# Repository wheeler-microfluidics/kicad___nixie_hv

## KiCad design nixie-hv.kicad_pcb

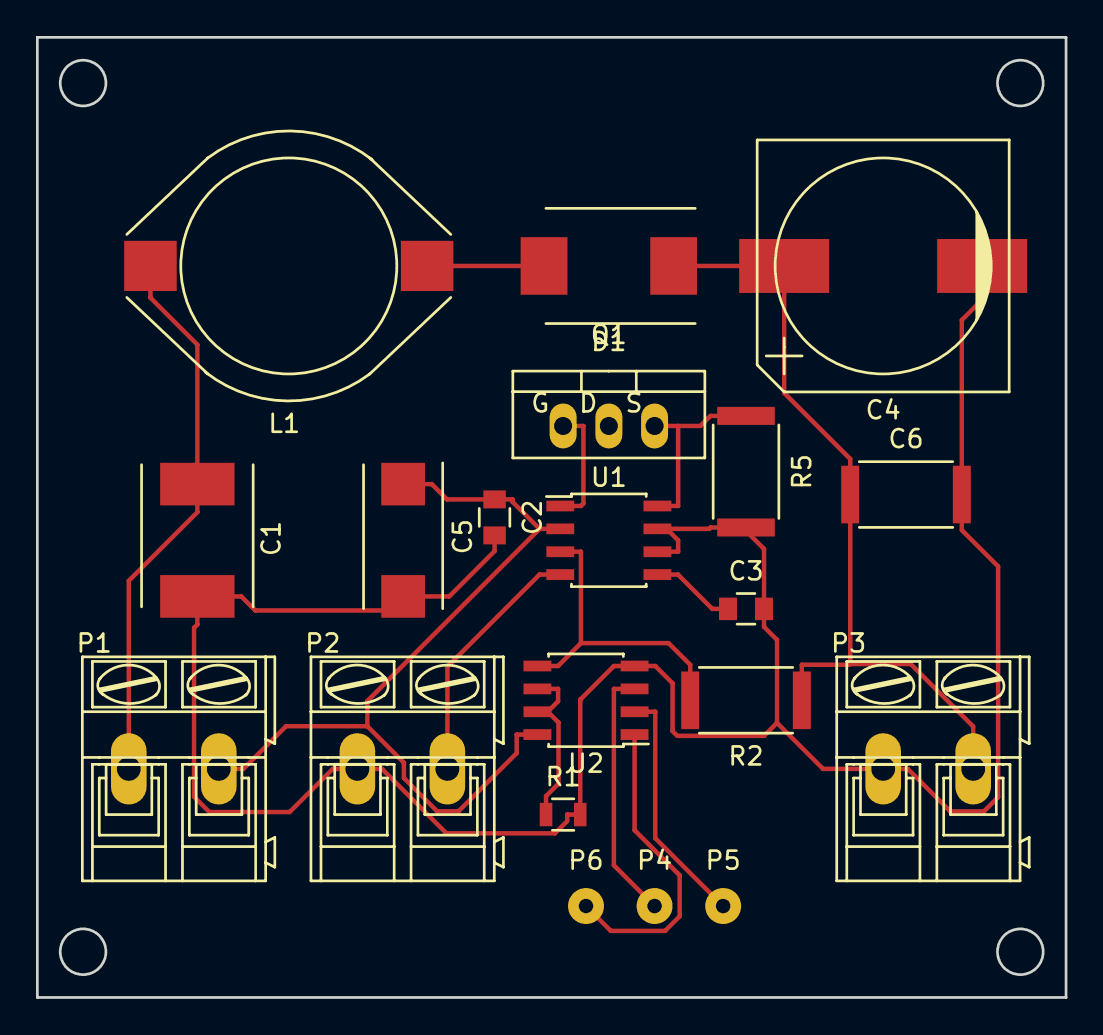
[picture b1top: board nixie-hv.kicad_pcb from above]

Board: 2 copper layers, 57.1 x 53.3 mm, 20 parts (0 on the bottom side), 14 nets.

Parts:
C1: 100uF, 35V; TantalC_SizeE_EIA-7360_Reflow
C2, C3: 100nF; C_0805
C4: 4u7,250V; C_SMD_12mm
C5: 10uF; TantalC_SizeD_EIA-7343_Reflow
C6: 100nF,250V; R_2512
D1: ES2F; DO-214AB
L1: 100uH; Inductor_18.54x15.24
P1: J1; AK300-2
P2: J2; AK300-2
P3: J3; AK300-2
P4, P5, P6: CONN_01X01; SolderWirePad_single_0-8mmDrill
Q1: IRF644PBF; TO-220_FET-GDS_Vertical
R1: 10k; R_0805
R2: 1M5; R_2512
R5: RSENSE; R_2512
U1: MAX1771_IC; SOIC-8_3.9x4.9mm_Pitch1.27mm
U2: MCP41050; SOIC-8_3.9x4.9mm_Pitch1.27mm

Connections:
GNDD: C1.2, C2.2, C3.2, C4.2, C5.2, C6.2, P2.1, P3.1, R1.2, R5.2, U1.6, U1.7, U2.4
unnamed: C1.1, L1.2, P1.1
unnamed: C2.1, C5.1, P1.2, U1.2, U2.8
unnamed: C3.1, U1.5
unnamed: C4.1, C6.1, D1.1, P3.2, R2.1
unnamed: D1.2, L1.1
unnamed: P2.2, U1.4
unnamed: P4.1, U2.3
unnamed: P5.1, U2.2
unnamed: P6.1, U2.1
unnamed: Q1.G, U1.1
unnamed: Q1.S, R5.1, U1.8
unnamed: R1.1, U2.6, U2.7
unnamed: R2.2, U1.3, U2.5

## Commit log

2015-10-09 Add gerber files and drill file
2017-07-13 added appveyor.yml
2017-07-14 AppVeyor Configuration Updated
2017-07-18 AppVeyor Update: "a4e909ac7a44d2708564d46a9b978b95c8367686"
2017-07-19 AppVeyor Update: "d5d159050eac48ab9123f383fe8e949476d7f60f"
2017-07-20 AppVeyor Update: "35852f667457a927c170bb71278740b12d7a8f75"
